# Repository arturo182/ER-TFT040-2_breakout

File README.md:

# ER-TFT040-2 Breakout

A quick breakout board for the 4.0" 480x480 TFT LCD, available from here: https://www.buydisplay.com/4-inch-tft-lcd-display-480x480-pixel-with-mipi-interface-for-iot-devices

Datasheet: https://www.buydisplay.com/download/manual/ER-TFT040-2_Datasheet.pdf

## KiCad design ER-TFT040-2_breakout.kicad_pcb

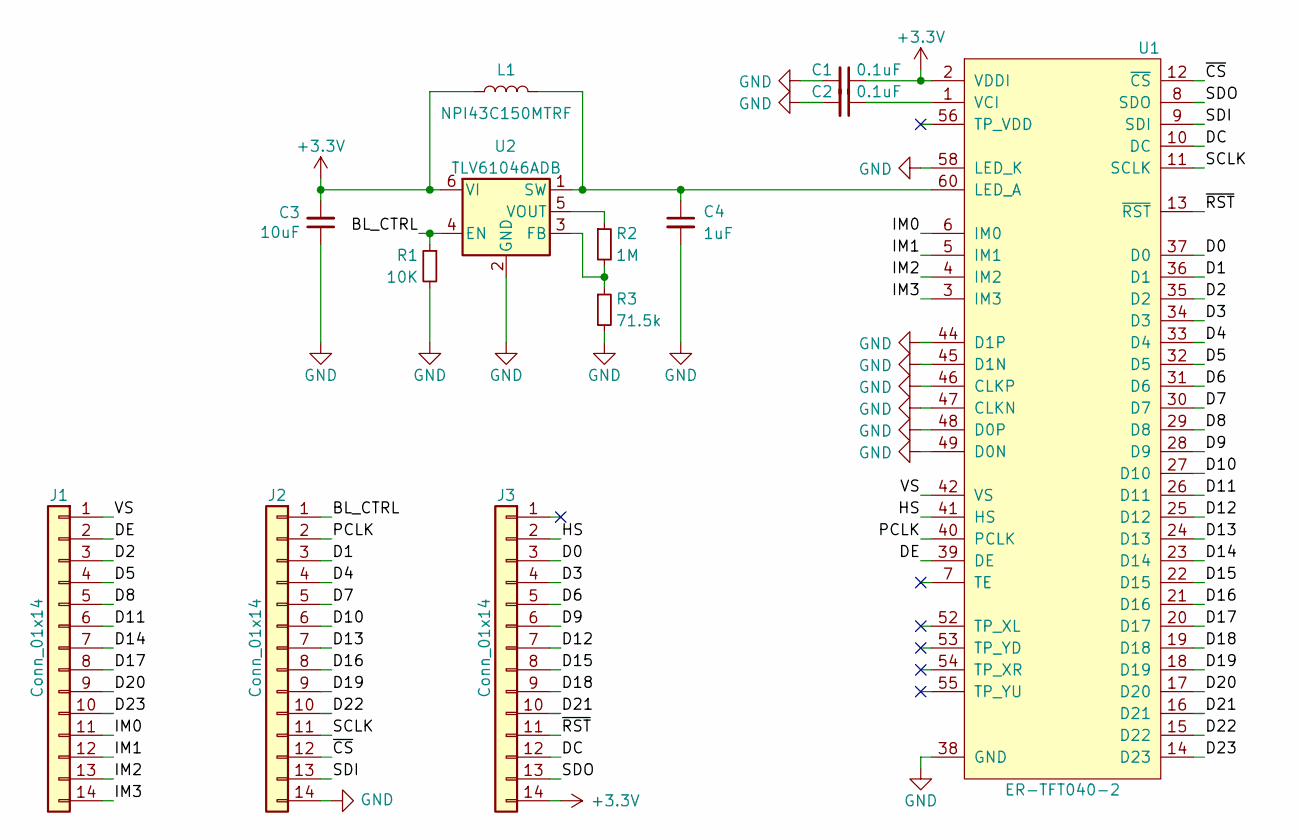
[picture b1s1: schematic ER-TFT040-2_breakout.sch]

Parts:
C1, C2: 0.1uF; C_0603_1608Metric
C3: 10uF; C_0603_1608Metric
C4: 1uF; C_0603_1608Metric
J1, J2, J3: Conn_01x14; PinHeader_1x14_P2.54mm_Vertical
L1: NPI43C150MTRF; L_Taiyo-Yuden_NR-50xx
R1: 10K; R_0603_1608Metric
R2: 1M; R_0603_1608Metric
R3: 71.5k; R_0603_1608Metric
U1: ER-TFT040-2; Molex_54132-5033_1x60-1MP_P0.5mm_Horizontal
U2: TLV61046ADB; SOT-23-6

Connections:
+3V3: C1.1, C3.2, J3.14, L1.1, U1.2 (VDDI), U2.6 (VI)
/BL_CTRL: J2.1, R1.1, U2.4 (EN)
/D0: J3.3, U1.37 (D0)
/D1: J2.3, U1.36 (D1)
/D2: J1.3, U1.35 (D2)
/D3: J3.4, U1.34 (D3)
/D4: J2.4, U1.33 (D4)
/D5: J1.4, U1.32 (D5)
/D6: J3.5, U1.31 (D6)
/D7: J2.5, U1.30 (D7)
/D8: J1.5, U1.29 (D8)
/D9: J3.6, U1.28 (D9)
/D10: J2.6, U1.27 (D10)
/D11: J1.6, U1.26 (D11)
/D12: J3.7, U1.25 (D12)
/D13: J2.7, U1.24 (D13)
/D14: J1.7, U1.23 (D14)
/D15: J3.8, U1.22 (D15)
/D16: J2.8, U1.21 (D16)
/D17: J1.8, U1.20 (D17)
/D18: J3.9, U1.19 (D18)
/D19: J2.9, U1.18 (D19)
/D20: J1.9, U1.17 (D20)
/D21: J3.10, U1.16 (D21)
/D22: J2.10, U1.15 (D22)
/D23: J1.10, U1.14 (D23)
/DC: J3.12, U1.10 (DC)
/DE: J1.2, U1.39 (DE)
/HS: J3.2, U1.41 (HS)
/IM0: J1.11, U1.6 (IM0)
/IM1: J1.12, U1.5 (IM1)
/IM2: J1.13, U1.4 (IM2)
/IM3: J1.14, U1.3 (IM3)
/PCLK: J2.2, U1.40 (PCLK)
/SCLK: J2.11, U1.11 (SCLK)
/SDI: J2.13, U1.9 (SDI)
/SDO: J3.13, U1.8 (SDO)
/VS: J1.1, U1.42 (VS)
/~CS~: J2.12, U1.12 (~CS~)
/~RST~: J3.11, U1.13 (~RST~)
GND: C1.2, C2.2, C3.1, C4.2, J2.14, R1.2, R3.2, U1.38 (GND), U1.43 (GND), U1.44 (D1P), U1.45 (D1N), U1.46 (CLKP), U1.47 (CLKN), U1.48 (D0P), U1.49 (D0N), U1.50 (GND), U1.57 (GND), U1.58 (LED_K), U1.59 (LED_K), U2.2 (GND)
unnamed: C2.1, U1.1 (VCI)
unnamed: C4.1, L1.2, U1.60 (LED_A), U2.1 (SW)
unnamed: R2.1, U2.5 (VOUT)
unnamed: R2.2, R3.1, U2.3 (FB)

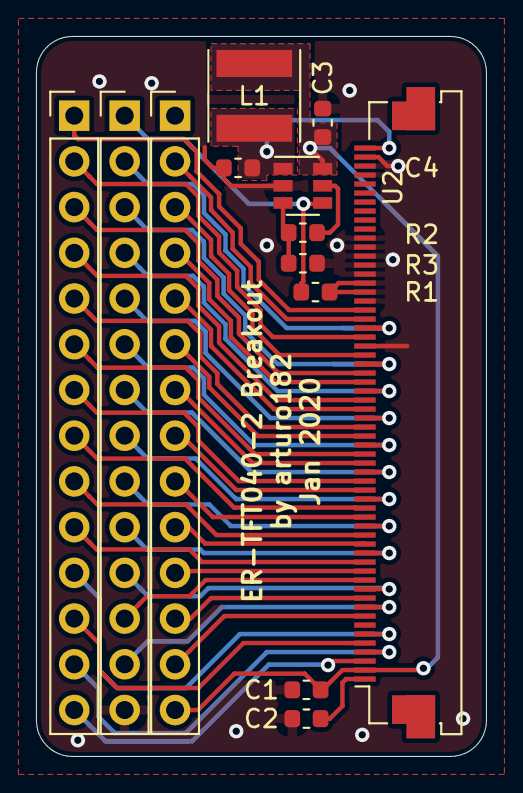
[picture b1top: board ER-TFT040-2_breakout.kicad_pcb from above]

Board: 2 copper layers, 25.0 x 40.0 mm, 13 parts (0 on the bottom side), 45 nets.

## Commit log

2020-01-14 Rev 1
